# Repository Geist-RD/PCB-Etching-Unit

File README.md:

# Board Etching Unit (BEU)

The **BEU** assists in the etching of PCB'S using FeCl<sub>3</sub>, so the operator gets to do more interesting things in the meantime.
BEU aims to achieve the following goals
- [ ] material cost below 50€
- [ ] moving FeCl<sub>3</sub> container
- [ ] FeCl<sub>3</sub> heater
  - [ ] open loop
  - [ ] closed loop control using thermoelement
- [ ] timer
- [ ] speed control

## Revision 0
- [ ] material cost below 50€
- [X] moving FeCl<sub>3</sub> container
- [ ] FeCl<sub>3</sub> heater
  - [ ] open loop
  - [ ] closed loop control using thermoelement
- [x] timer
- [x] speed control

### Assembly
Two DC motors will move the FeCl<sub>3</sub> container directly by connecting to drilled holes.\
A 3D-printed support beam will hold the motors at a sufficient height.
Desired dimensions can be configured in the OpenScad-file.\
This should enable the operator to choose a container of arbitrary width or length. If a chosen container
is small enough to be held by one motor, a single support beam with a counterweight can be used.

### PCB
In the spirit of this project, the board will be etched by the operator.\
The operator can read up on the procedure [here](https://www.electricstuff.co.uk/pcbs.html), it's the best primer for selfmade PCB's we've found so far.

### Comments
Used my dormant Arduino Uno board for revision 0. A dev board for 20€ is fine for revision 0 but it did screw over the goal of low material cost.
Following revisions might use a PIC, the instruction set seems compact enough for some assembly and I found several primers covering them (IDE: PIKDEV).\
Though the AVR software will be done in C for now.\
Since I'm using a plastic container, I skipped on heating the FeCl<sub>3</sub> this time. Aluminium seems to be easy to solder/weld, might be used for later revisions.\
Closed loop temperature controll could be done using a PT100 or Typ K element, if the casing survives extended exposure to FeCl<sub>3</sub>.

The board just etches on one side, with the other one facing down. A support beam could hold it up, but the support itself would cover parts of the board too.\
Vertical support on the left and right with 1 mm width could work.

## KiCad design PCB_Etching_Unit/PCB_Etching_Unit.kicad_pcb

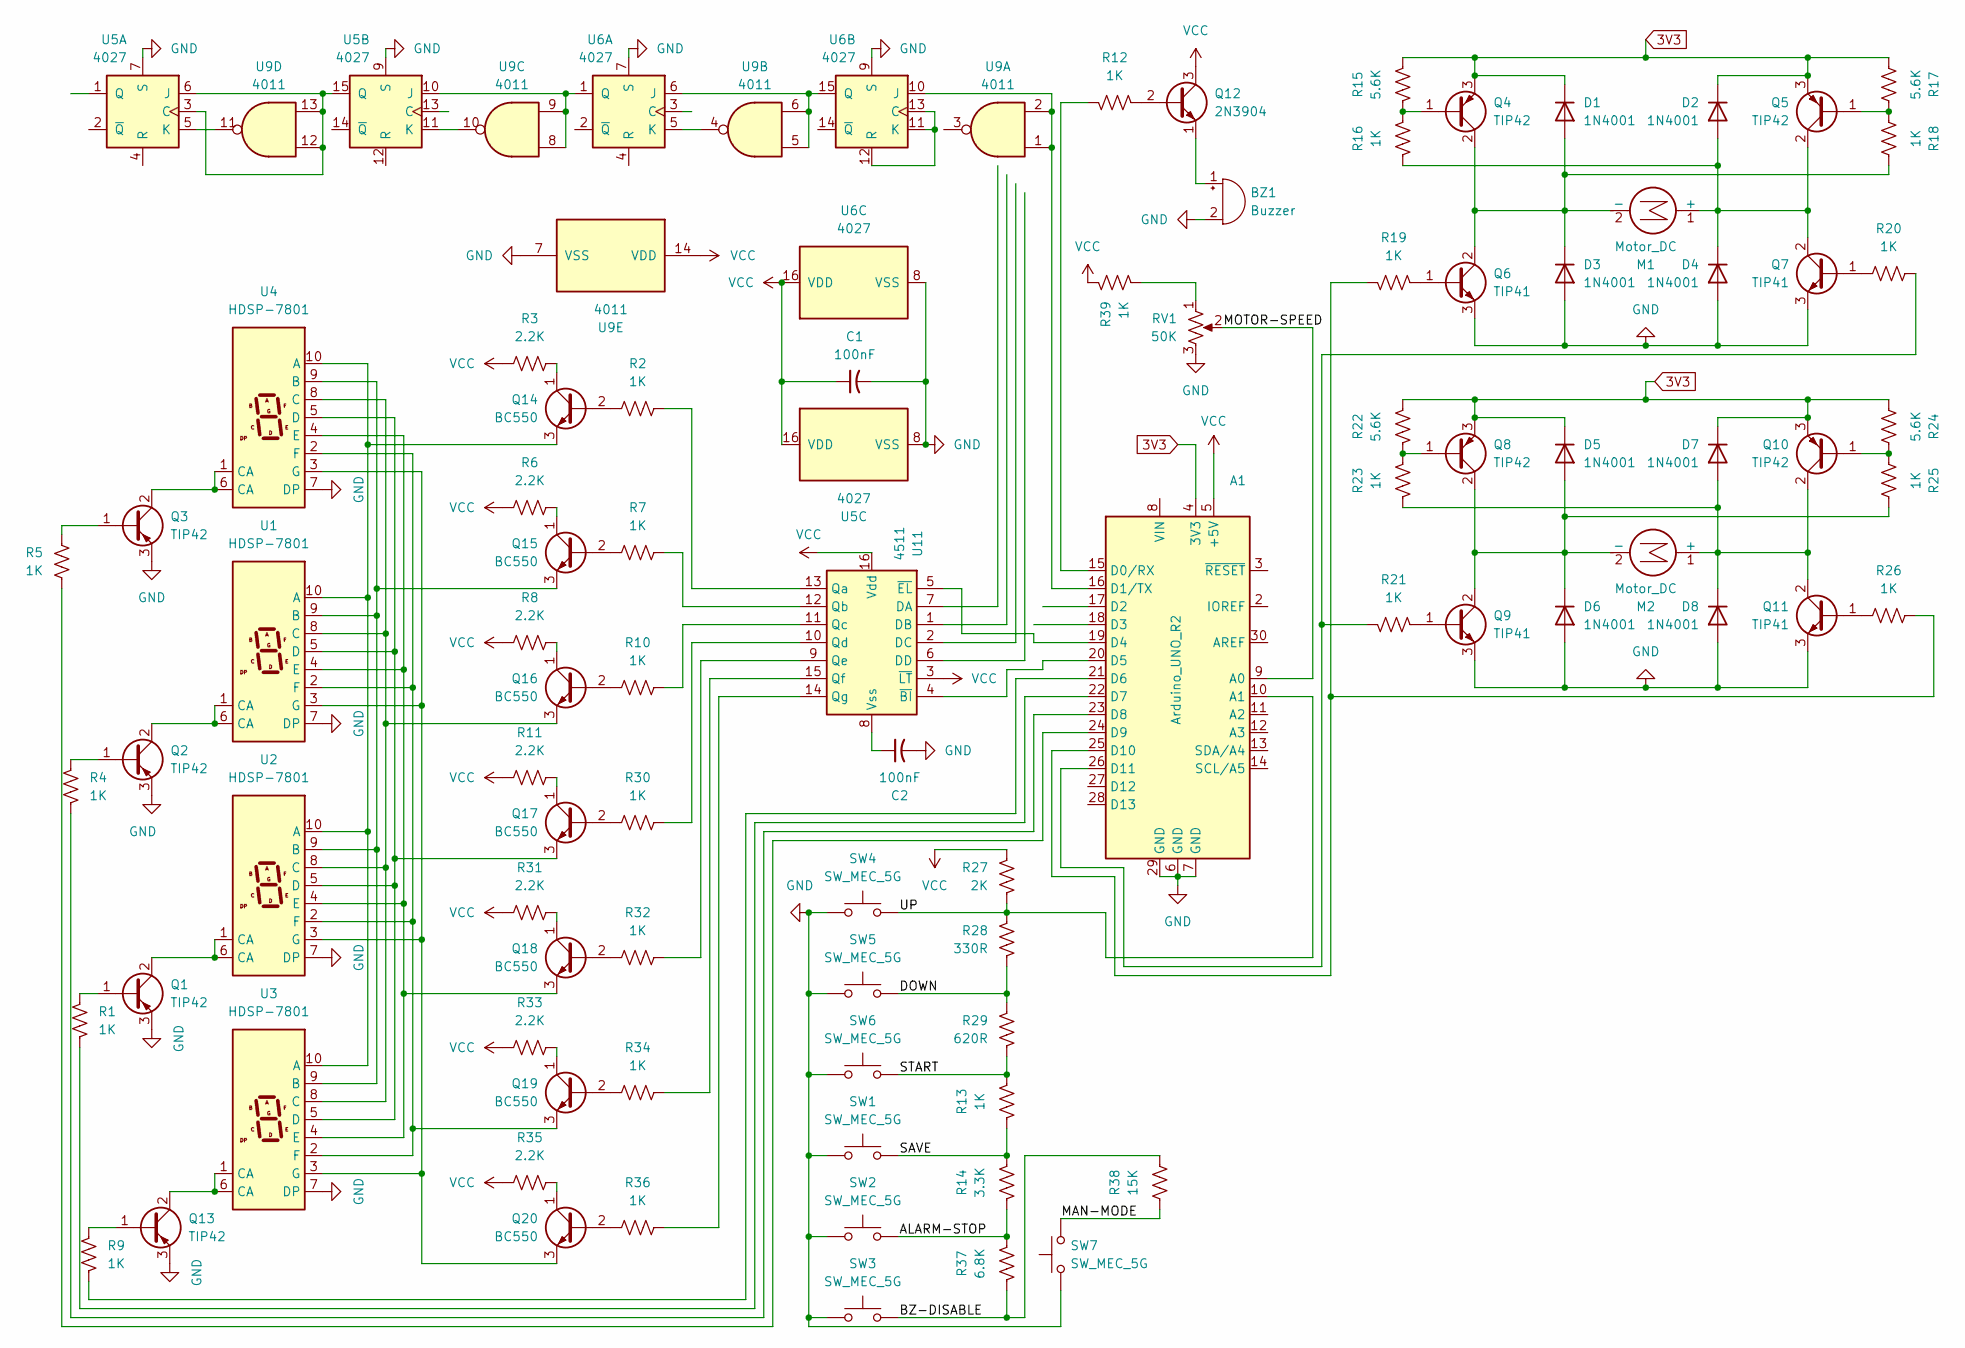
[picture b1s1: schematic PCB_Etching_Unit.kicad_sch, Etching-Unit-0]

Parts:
A1: Arduino_UNO_R2
BZ1: Buzzer; Buzzer_12x9.5RM7.6
C1, C2: 100nF
D1, D2, D3, D4, D5, D6, D7, D8: 1N4001; D_DO-41_SOD81_P10.16mm_Horizontal
M1, M2: Motor_DC; PinHeader_1x02_P2.54mm_Vertical
Q1, Q2, Q3, Q13: TIP42; TO-220-3_Horizontal_TabDown
Q4, Q5, Q8, Q10: TIP42; TO-220-3_Vertical
Q6, Q7, Q9, Q11: TIP41; TO-220-3_Vertical
Q12: 2N3904; TO-92_Inline
Q14, Q15, Q16, Q17, Q18, Q19, Q20: BC550; TO-92_Inline
R1, R2, R4, R5, R7, R9, R10, R12, R13, R16, R18, R19, R20, R21, R23, R25, R26, R30, R32, R34, R36, R39: 1K; R_Axial_DIN0204_L3.6mm_D1.6mm_P7.62mm_Horizontal
R3, R6, R8, R11, R31, R33, R35: 2.2K; R_Axial_DIN0204_L3.6mm_D1.6mm_P7.62mm_Horizontal
R14: 3.3K; R_Axial_DIN0204_L3.6mm_D1.6mm_P7.62mm_Horizontal
R15, R17, R22, R24: 5.6K; R_Axial_DIN0204_L3.6mm_D1.6mm_P7.62mm_Horizontal
R27: 2K; R_Axial_DIN0204_L3.6mm_D1.6mm_P7.62mm_Horizontal
R28: 330R; R_Axial_DIN0204_L3.6mm_D1.6mm_P7.62mm_Horizontal
R29: 620R; R_Axial_DIN0204_L3.6mm_D1.6mm_P7.62mm_Horizontal
R37: 6.8K; R_Axial_DIN0204_L3.6mm_D1.6mm_P7.62mm_Horizontal
R38: 15K; R_Axial_DIN0204_L3.6mm_D1.6mm_P7.62mm_Horizontal
RV1: 50K; Potentiometer_Bourns_3214G_Horizontal
SW1, SW2, SW3, SW4, SW5, SW6, SW7: SW_MEC_5G; SW_MEC_5GSH9
U1, U2, U3, U4: HDSP-7801
U5: 4027; DIP-16_W7.62mm
U6: 4027
U9: 4011; DIP-14_W7.62mm
U11: 4511

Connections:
3V3: A1.4 (3V3), D1.1 (K), D2.1 (K), D5.1 (K), D7.1 (K), Q4.3 (E), Q5.3 (E), Q8.3 (E), Q10.3 (E), R15.1, R17.1, R22.1, R24.1
/ALARM-STOP: R14.2, R37.1, SW2.1 (A), SW2.2 (A)
/BZ-DISABLE: R37.2, R38.2, SW3.1 (A), SW3.2 (A)
/DOWN: R28.1, R29.2, SW5.1 (A), SW5.2 (A)
/MAN-MODE: R38.1, SW7.1 (A), SW7.2 (A)
/SAVE: R13.2, R14.1, SW1.1 (A), SW1.2 (A)
/START: R13.1, R29.1, SW6.1 (A), SW6.2 (A)
/UP: A1.10 (A1), R27.1, R28.2, SW4.1 (A), SW4.2 (A)
GND: A1.6 (GND), A1.7 (GND), A1.29 (GND), BZ1.2 (-), C1.2, C2.2, D3.2 (A), D4.2 (A), D6.2 (A), D8.2 (A), Q1.3 (E), Q2.3 (E), Q3.3 (E), Q6.3 (E), Q7.3 (E), Q9.3 (E), Q11.3 (E), Q13.3 (E), RV1.3, SW1.3 (B), SW1.4 (B), SW2.3 (B), SW2.4 (B), SW3.3 (B), SW3.4 (B), SW4.3 (B), SW4.4 (B), SW5.3 (B), SW5.4 (B), SW6.3 (B), SW6.4 (B), SW7.3 (B), SW7.4 (B), U1.7 (DP), U2.7 (DP), U3.7 (DP), U4.7 (DP), U5.7 (S), U5.8 (VSS), U5.9 (S), U6.7 (S), U6.8 (VSS), U6.9 (S), U9.7 (VSS)
unnamed: A1.9 (A0), RV1.2
unnamed: A1.15 (D0/RX), R12.2
unnamed: A1.16 (D1/TX), U6.10 (J), U9.1, U9.2
unnamed: A1.19 (D4), U11.5 (~EL)
unnamed: A1.20 (D5), U11.4 (~BI)
unnamed: A1.21 (D6), R9.2
unnamed: A1.22 (D7), R1.2
unnamed: A1.23 (D8), R4.2
unnamed: A1.24 (D9), R5.2
unnamed: BZ1.1 (+), Q12.1 (E)
unnamed: C2.1, U11.8 (Vss)
unnamed: D1.2 (A), D3.1 (K), M1.2 (-), Q4.2 (C), Q6.2 (C), R18.2
unnamed: D2.2 (A), D4.1 (K), M1.1 (+), Q5.2 (C), Q7.2 (C), R16.2
unnamed: D5.2 (A), D6.1 (K), M2.2 (-), Q8.2 (C), Q9.2 (C), R25.2
unnamed: D7.2 (A), D8.1 (K), M2.1 (+), Q10.2 (C), Q11.2 (C), R23.2
unnamed: Q1.1 (B), R1.1
unnamed: Q1.2 (C), U2.1 (CA), U2.6 (CA)
unnamed: Q2.1 (B), R4.1
unnamed: Q2.2 (C), U1.1 (CA), U1.6 (CA)
unnamed: Q3.1 (B), R5.1
unnamed: Q3.2 (C), U4.1 (CA), U4.6 (CA)
unnamed: Q4.1 (B), R15.2, R16.1
unnamed: Q5.1 (B), R17.2, R18.1
unnamed: Q6.1 (B), R19.1
unnamed: Q7.1 (B), R20.1
unnamed: Q8.1 (B), R22.2, R23.1
unnamed: Q9.1 (B), R21.1
unnamed: Q10.1 (B), R24.2, R25.1
unnamed: Q11.1 (B), R26.1
unnamed: Q12.2 (B), R12.1
unnamed: Q13.1 (B), R9.1
unnamed: Q13.2 (C), U3.1 (CA), U3.6 (CA)
unnamed: Q14.2 (B), R2.1
unnamed: Q14.1 (C), R3.1
unnamed: Q14.3 (E), U1.10 (A), U2.10 (A), U3.10 (A), U4.10 (A)
unnamed: Q15.2 (B), R7.1
unnamed: Q15.1 (C), R6.2
unnamed: Q15.3 (E), U1.9 (B), U2.9 (B), U3.9 (B), U4.9 (B)
unnamed: Q16.2 (B), R10.1
unnamed: Q16.1 (C), R8.2
unnamed: Q16.3 (E), U1.8 (C), U2.8 (C), U3.8 (C), U4.8 (C)
unnamed: Q17.2 (B), R30.1
unnamed: Q17.1 (C), R11.2
unnamed: Q17.3 (E), U1.5 (D), U2.5 (D), U3.5 (D), U4.5 (D)
unnamed: Q18.2 (B), R32.1
unnamed: Q18.1 (C), R31.2
unnamed: Q18.3 (E), U1.4 (E), U2.4 (E), U3.4 (E), U4.4 (E)
unnamed: Q19.2 (B), R34.1
unnamed: Q19.1 (C), R33.2
unnamed: Q19.3 (E), U1.2 (F), U2.2 (F), U3.2 (F), U4.2 (F)
unnamed: Q20.2 (B), R36.1
unnamed: Q20.1 (C), R35.2
unnamed: Q20.3 (E), U1.3 (G), U2.3 (G), U3.3 (G), U4.3 (G)
unnamed: R39.1, RV1.1
unnamed: U5.3 (C), U5.6 (J), U5.15 (Q), U9.12, U9.13
unnamed: U5.5 (K), U9.11
unnamed: U5.10 (J), U6.1 (Q), U9.8, U9.9
unnamed: U5.11 (K), U9.10
unnamed: U6.11 (K), U6.12 (R), U6.13 (C)
unnamed: U6.6 (J), U6.15 (Q), U9.5, U9.6
unnamed: U6.5 (K), U9.4
unnamed: R2.2, U11.13 (Qa)
unnamed: R7.2, U11.12 (Qb)
unnamed: R10.2, U11.11 (Qc)
unnamed: R30.2, U11.10 (Qd)
unnamed: R32.2, U11.9 (Qe)
unnamed: R34.2, U11.15 (Qf)
unnamed: R36.2, U11.14 (Qg)
VCC: A1.5 (+5V), C1.1, Q12.3 (C), R3.2, R6.1, R8.1, R11.1, R27.2, R31.1, R33.1, R35.1, R39.2, U5.16 (VDD), U6.16 (VDD), U9.14 (VDD), U11.3 (~LT), U11.16 (Vdd)

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
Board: 2 copper layers, 85 parts (0 on the bottom side), 68 nets, no tracks yet.

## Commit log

2025-12-22 Revision 0 of PCB etching unit
2025-12-22 Added PDF of revision 0
2025-12-23 Fixed wrong pnp, npn bjt orientation of 7-segment-display.
2025-12-23 Added label definitions and moved some parts around.
2025-12-23 Added poti for speed control and manual mode button.
2025-12-23 Updated readme file
2025-12-23 Previously messed up shift register wiring. Fixed now
2025-12-23 Fixed typos in label table
2025-12-23 4511 pulls output low to activate, replaced NPN with PNP transistors to do that
2025-12-23 Updated doc
2025-12-23 Yapping in readme
2025-12-23 Next person to mix up PNP transistors gets bolted. Flipped transistors at segment output
2025-12-23 Put PIC IDE in Readme so I don't forget it later
2025-12-23 Trying out PlatformIO with bare C
2025-12-23 Putting a framework veil over madness doesn't seem worth it. Using bare C, avr-gcc and avrdude instead
2025-12-23 Learned how to use CMake-GUI for embedded stuff, wiki is surprisingly good. Celebratory cigarette break
2025-12-24 Starting on PCB layout and added assembly, pcb production link in readme
2025-12-24 Pin 25, 26 at Arduino had to be switched for layout reasons.
2025-12-24 Typo in readme, devastated
2025-12-25 Got critized for layout, devastated
2025-12-26 Added layout for voltage ladder/pushbuttons
